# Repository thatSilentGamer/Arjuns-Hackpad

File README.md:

# Arjun's Hackpad

Arjun's Hackpad is an 8-key macropad with a rotary encoder, OLED display, and underglow RGB lighting. It uses custom QMK firmware with advanced features like RGB mode cycling and a toggleable encoder with 4 different modes.

## Features

* 8-key layout (2 rows × 4 columns)
* OLED Display showing encoder mode and RGB status
* EC11 Rotary encoder with 4 switchable modes (Volume, Brightness, Media, Scroll)
* 16x SK6812 MINI-E RGB LEDs (2 per key) for vibrant underglow
* Custom QMK firmware with advanced RGB and encoder control

## CAD Model

The case consists of two 3D printed parts held together with M3 hardware:
* **Top piece** - Contains 4 heatset inserts for mounting
* **Bottom piece** - Screws pass through bottom into top inserts
* Assembly uses 4x M3×16mm screws and 4x M3×5×4mm heatset inserts

## PCB

**PCB Specifications:**
* Dimensions: 78.72mm × 98.51mm
* 2-layer design
* Matrix wired as 2 rows × 4 columns with COL2ROW diode direction
* Seeed XIAO RP2040 microcontroller

### Schematic

The design uses a standard keyboard matrix with diodes. RGB LEDs are chained on GPIO4, OLED uses I2C on GPIO6/GPIO7, and the rotary encoder connects to GPIO0/GPIO1.

## Firmware

This hackpad uses **QMK firmware.**

### Key Layout:
```
[RGB Cycle] [Enc Toggle] [Play/Pause] [Next Track]
[   Copy  ] [   Paste  ] [   Undo   ] [   Redo   ]
```

### Features:
* **RGB Cycle (Key 1)**: Cycles through the 10 RGB animation modes
* **Encoder Toggle (Key 2)**: Switches encoder between 4 modes:
  1. Volume Up/Down
  2. Brightness Up/Down
  3. Media Next/Previous
  4. Scroll Up/Down
* **Media Controls**: Play/Pause and Next Track
* **Editing Shortcuts**: Copy, Paste, Undo, Redo
* **OLED Display**: Shows current encoder mode and RGB status

## BOM

Here's everything you need to build this hackpad:

* 1x Seeed XIAO RP2040
* 8x MX-Style switches
* 8x White blank DSA keycaps
* 8x 1N4148 DO-35 Diodes
* 16x SK6812 MINI-E RGB LEDs
* 1x 0.91" 128x32 OLED Display
* 1x EC11 Rotary Encoder
* 4x M3×16mm screws
* 4x M3×5×4mm heatset inserts
* 1x Custom PCB
* 1x 3D printed case

## Production Files

All manufacturing files are included in the `production/` folder:
* `gerbers.zip` - PCB manufacturing files
* `firmware.hex` - Compiled QMK firmware
* `Top.step` - 3D printable top part
* `Bottom.step` - 3D printable bottom part

## Assembly Instructions

1. Print the case parts
2. Install heatset inserts into the 4 mounting holes in the top piece
3. Solder components to the PCB:
   - Diodes
   - RGB LEDs
   - OLED display
   - Rotary encoder
   - XIAO RP2040
4. Flash firmware to the XIAO RP2040
5. Install switche* into the PCB
6. Add keycaps to switches
7. Mount PCB into bottom case
8. Attach top case using 4x M3×16mm screws through bottom case part into heatset inserts

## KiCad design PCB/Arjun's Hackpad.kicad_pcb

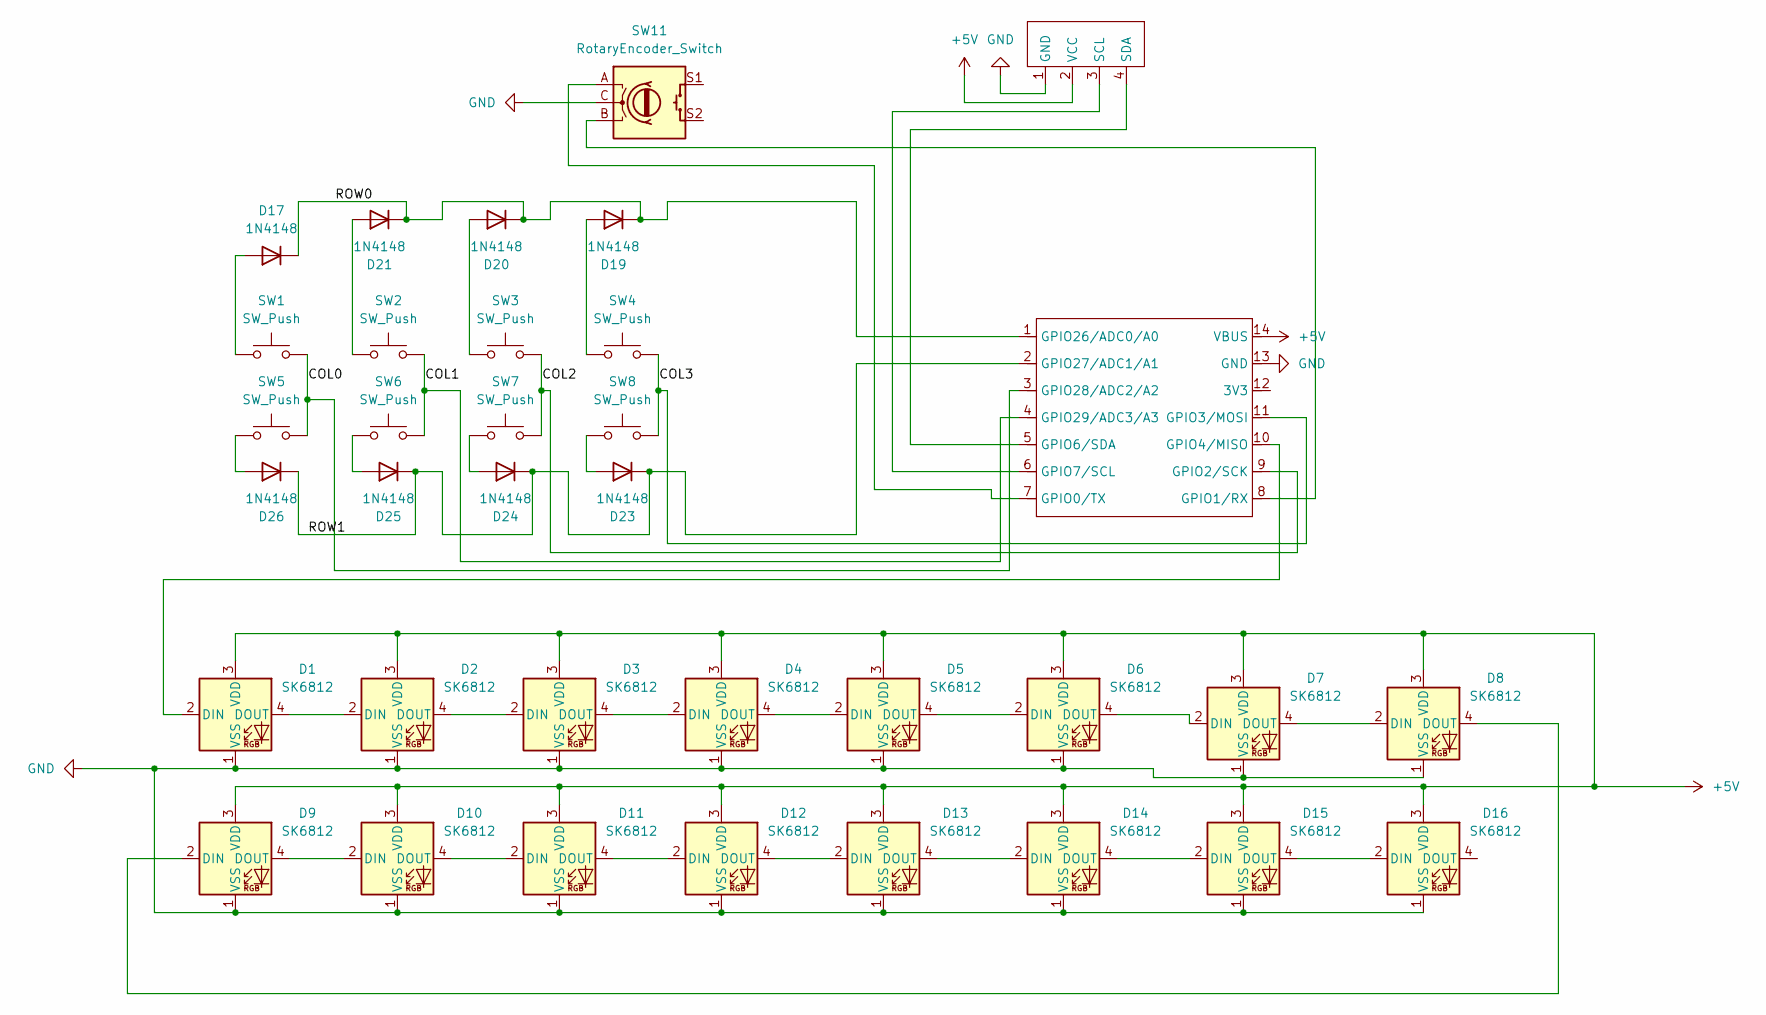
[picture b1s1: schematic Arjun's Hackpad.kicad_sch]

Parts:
D1, D2, D3, D4, D5, D6, D7, D8, D9, D10, D11, D12, D13, D14, D15, D16: SK6812; LED_SK6812_PLCC4_5.0x5.0mm_P3.2mm
D17, D19, D20, D21, D23, D24, D25, D26: 1N4148; D_A-405_P2.54mm_Vertical_AnodeUp
SW1, SW2, SW3, SW4, SW5, SW6, SW7, SW8: SW_Push; SW_Cherry_MX_1.00u_PCB
SW11: RotaryEncoder_Switch; RotaryEncoder_Alps_EC11E-Switch_Vertical_H20mm_CircularMoun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
U1: XIAO-RP2040-DIP
U3: SSD1306-0.91-OLED-4pin-128x32

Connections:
+5V: D1.3 (VDD), D2.3 (VDD), D3.3 (VDD), D4.3 (VDD), D5.3 (VDD), D6.3 (VDD), D7.3 (VDD), D8.3 (VDD), D9.3 (VDD), D10.3 (VDD), D11.3 (VDD), D12.3 (VDD), D13.3 (VDD), D14.3 (VDD), D15.3 (VDD), D16.3 (VDD), U1.14 (VBUS), U3.2 (VCC)
/COL0: SW1.2, SW5.2, U1.3 (GPIO28/ADC2/A2)
/COL1: SW2.2, SW6.2, U1.4 (GPIO29/ADC3/A3)
/COL2: SW3.2, SW7.2, U1.9 (GPIO2/SCK)
/COL3: SW4.2, SW8.2, U1.11 (GPIO3/MOSI)
/ROW0: D17.1 (K), D19.1 (K), D20.1 (K), D21.1 (K), U1.1 (GPIO26/ADC0/A0)
/ROW1: D23.1 (K), D24.1 (K), D25.1 (K), D26.1 (K), U1.2 (GPIO27/ADC1/A1)
GND: D1.1 (VSS), D2.1 (VSS), D3.1 (VSS), D4.1 (VSS), D5.1 (VSS), D6.1 (VSS), D7.1 (VSS), D8.1 (VSS), D9.1 (VSS), D10.1 (VSS), D11.1 (VSS), D12.1 (VSS), D13.1 (VSS), D14.1 (VSS), D15.1 (VSS), D16.1 (VSS), SW11.C, U1.13 (GND), U3.1 (GND)
unnamed: D1.2 (DIN), U1.10 (GPIO4/MISO)
unnamed: D1.4 (DOUT), D2.2 (DIN)
unnamed: D2.4 (DOUT), D3.2 (DIN)
unnamed: D3.4 (DOUT), D4.2 (DIN)
unnamed: D4.4 (DOUT), D5.2 (DIN)
unnamed: D5.4 (DOUT), D6.2 (DIN)
unnamed: D6.4 (DOUT), D7.2 (DIN)
unnamed: D7.4 (DOUT), D8.2 (DIN)
unnamed: D8.4 (DOUT), D9.2 (DIN)
unnamed: D9.4 (DOUT), D10.2 (DIN)
unnamed: D10.4 (DOUT), D11.2 (DIN)
unnamed: D11.4 (DOUT), D12.2 (DIN)
unnamed: D12.4 (DOUT), D13.2 (DIN)
unnamed: D13.4 (DOUT), D14.2 (DIN)
unnamed: D14.4 (DOUT), D15.2 (DIN)
unnamed: D15.4 (DOUT), D16.2 (DIN)
unnamed: D17.2 (A), SW1.1
unnamed: D19.2 (A), SW4.1
unnamed: D20.2 (A), SW3.1
unnamed: D21.2 (A), SW2.1
unnamed: D23.2 (A), SW8.1
unnamed: D24.2 (A), SW7.1
unnamed: D25.2 (A), SW6.1
unnamed: D26.2 (A), SW5.1
unnamed: SW11.A, U1.7 (GPIO0/TX)
unnamed: SW11.B, U1.8 (GPIO1/RX)
unnamed: U1.5 (GPIO6/SDA), U3.4 (SDA)
unnamed: U1.6 (GPIO7/SCL), U3.3 (SCL)

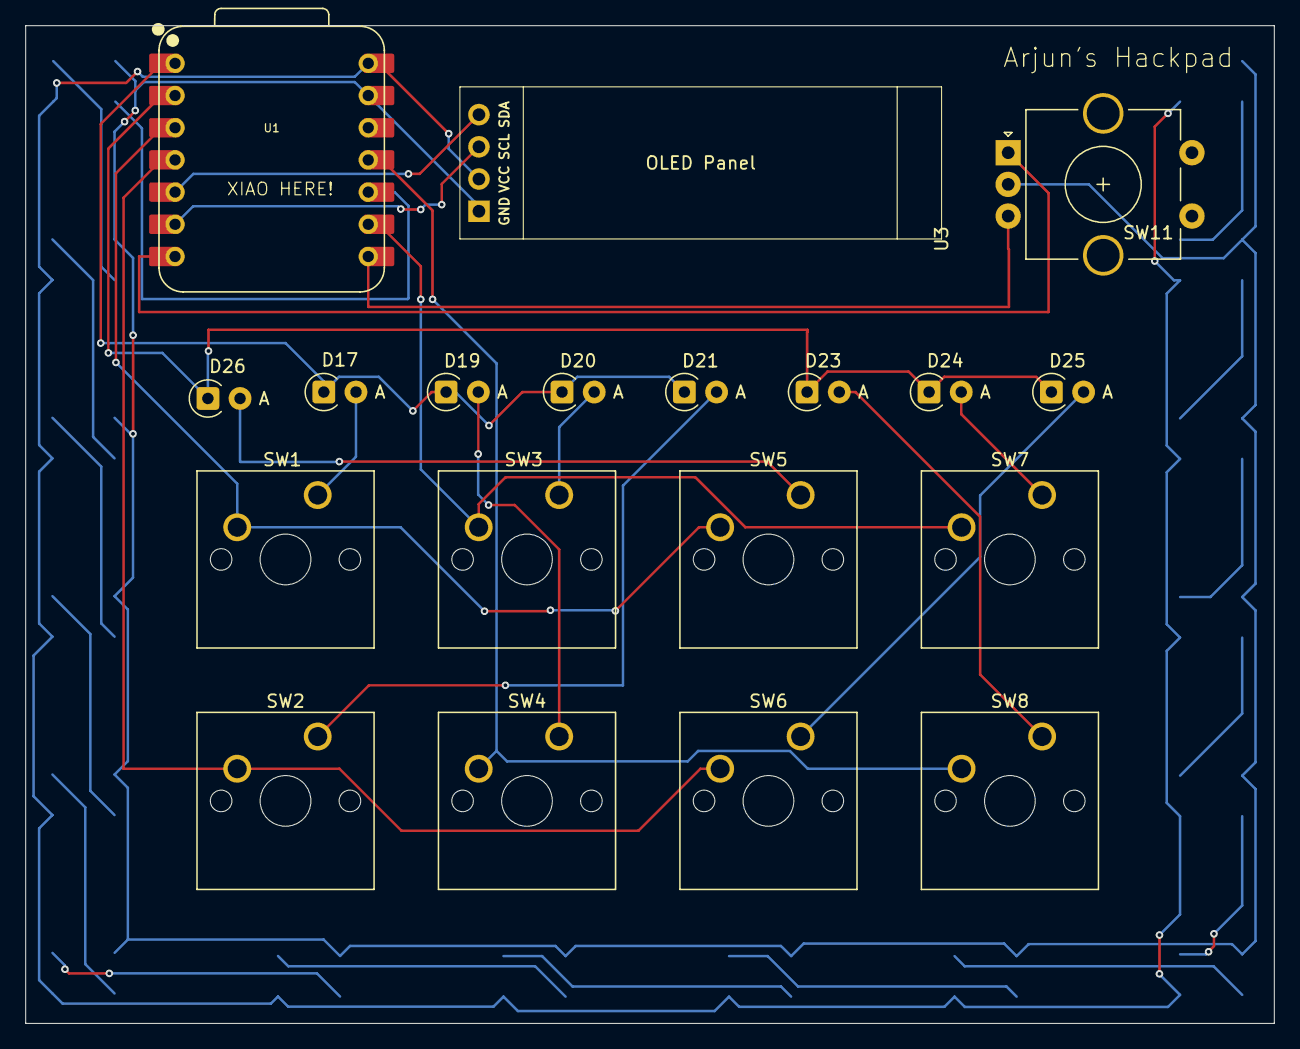
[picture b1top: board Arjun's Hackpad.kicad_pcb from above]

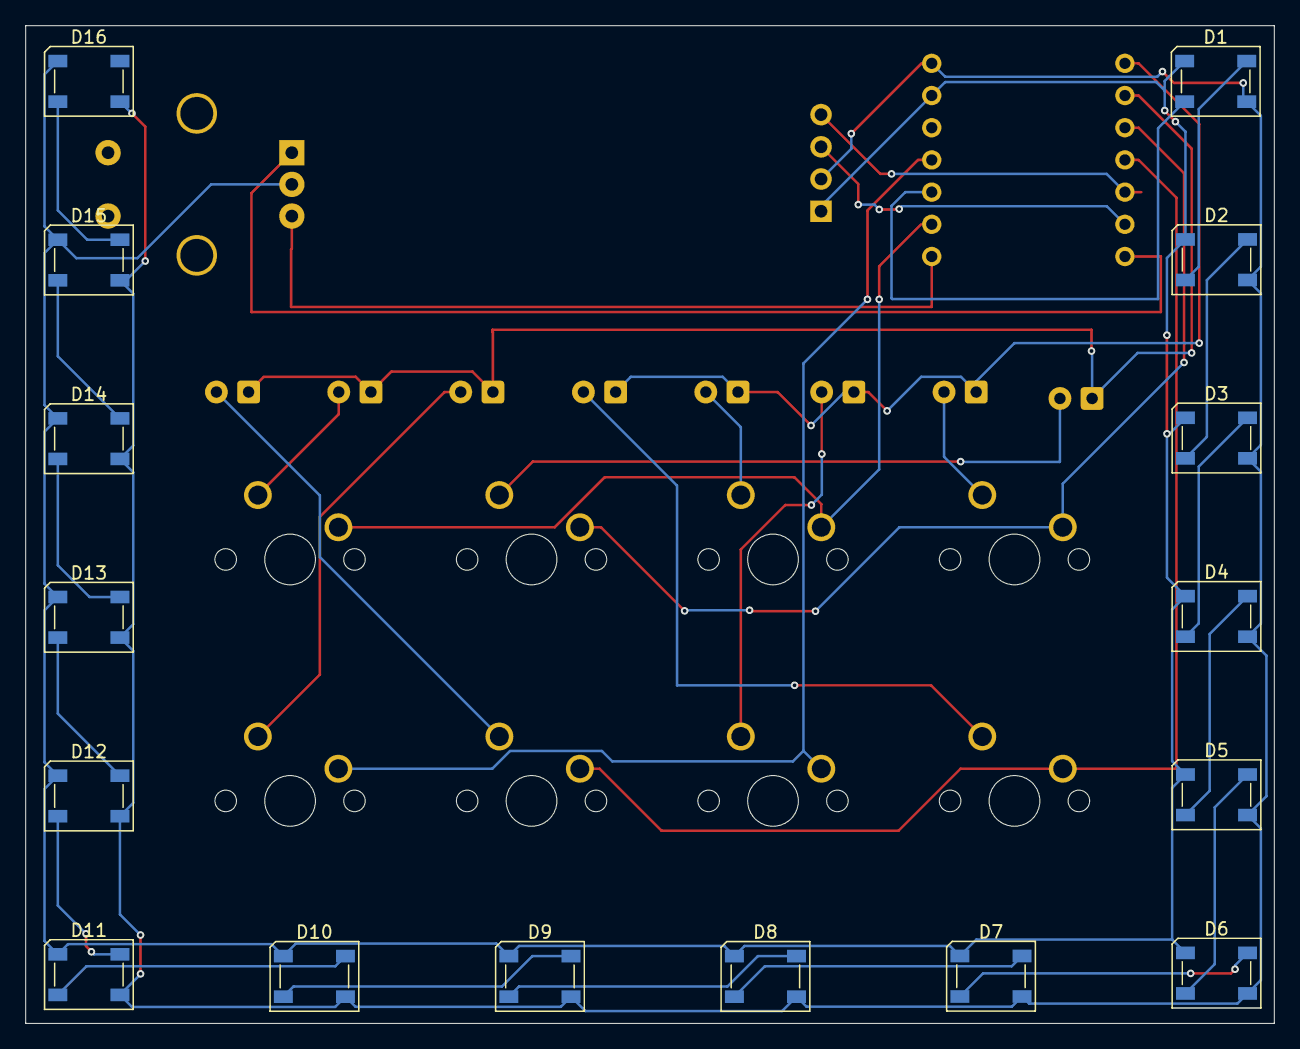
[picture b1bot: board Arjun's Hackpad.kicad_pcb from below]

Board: 2 copper layers, 98.5 x 78.7 mm, 35 parts (16 on the bottom side), 36 nets.

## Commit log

2026-02-13 Add complete project files and documentation
2026-02-13 Rename Screenshot 2026-02-13 185326.png to Bottom
2026-02-13 Rename Bottom to case_bottom
2026-02-13 Rename case_bottom to case_bottom.png
2026-02-14 Add BOM
2026-02-14 Update project files
2026-02-16 Add CAD source files and updated gerbers with corrected footprints
2026-02-16 Add updated images of cad and pcb
